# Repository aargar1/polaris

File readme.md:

# Polaris
Polaris is a feature-rich development board built around the Lattice iCE40 FPGA, designed for experimentation and small FPGA-based projects. The board provides a practical set of peripherals for graphics, storage, and USB-based interaction, all in a compact and approachable design. I designed it to implement a custom 32-bit microcontroller.

## Features

- Lattice iCE40 FPGA
- VGA output with audio support
- SD card interface
- 2× USB Type-A ports
- User-controllable LED
- GPIO and SPI headers

## Tooling

Polaris is plug-and-play compatable with the `yosys` toolchain. The [iCEStudio](https://icestudio.io/) development enviornment provides a great ecosystem for development on Polaris and iCE40-based boards in general.

## Acknowlegments

Thanks to the open-source FPGA and KiCad communities, whose tools and documentation made this project possible.

## BOM (Hack Club Blueprint)
| Comment             | Designator                      | Footprint        | LCSC Part # | Direct Link                                                                                              |
| ------------------- | ------------------------------- | ---------------- | ----------- | -------------------------------------------------------------------------------------------------------- |
| 2150                | R11,R3,R7                       | 0603             | C2960889    | [https://www.lcsc.com/product-detail/C2960889.html](https://www.lcsc.com/product-detail/C2960889.html)   |
| 2.7nF               | C15,C16                         | 0603             | C1609       | [https://www.lcsc.com/product-detail/C1609.html](https://www.lcsc.com/product-detail/C1609.html)         |
| Bus                 | J4                              | 2x14 2.54mm      | C725886     | [https://www.lcsc.com/product-detail/C725886.html](https://www.lcsc.com/product-detail/C725886.html)     |
| VGA                 | J1                              | ICD15S13E4GV00LF | C3121412    | [https://www.lcsc.com/product-detail/C3121412.html](https://www.lcsc.com/product-detail/C3121412.html)   |
| 74CBTLV3126PW,118   | U2                              | TSSOP-14         | C478017     | [https://www.lcsc.com/product-detail/C478017.html](https://www.lcsc.com/product-detail/C478017.html)     |
| 47k                 | R17,R19–R24,R27,R30,R31         | 0603             | C25819      | [https://www.lcsc.com/product-detail/C25819.html](https://www.lcsc.com/product-detail/C25819.html)       |
| WM8524CGEDT         | U3                              | TSSOP-16         | C146242     | [https://www.lcsc.com/product-detail/C146242.html](https://www.lcsc.com/product-detail/C146242.html)     |
| 1Ω                  | R28,R29                         | 0603             | C22936      | [https://www.lcsc.com/product-detail/C22936.html](https://www.lcsc.com/product-detail/C22936.html)       |
| NRS4018T2R2MDGJ     | L1                              | SRN4018          | C92959      | [https://www.lcsc.com/product-detail/C92959.html](https://www.lcsc.com/product-detail/C92959.html)       |
| W25Q16JVSNIQ        | U4                              | SOIC-8           | C115407     | [https://www.lcsc.com/product-detail/C115407.html](https://www.lcsc.com/product-detail/C115407.html)     |
| 330Ω                | R35,R36,R37                     | 0603             | C23138      | [https://www.lcsc.com/product-detail/C23138.html](https://www.lcsc.com/product-detail/C23138.html)       |
| TLV62568DBVR        | U7                              | SOT-23-5         | C163219     | [https://www.lcsc.com/product-detail/C163219.html](https://www.lcsc.com/product-detail/C163219.html)     |
| 100nF               | C1,C2,C3,C4,C5,C10,C14,C27,C30  | 0603             | C14663      | [https://www.lcsc.com/product-detail/C14663.html](https://www.lcsc.com/product-detail/C14663.html)       |
| SW_Push             | SW1                             | 6mm              | C455112     | [https://www.lcsc.com/product-detail/C455112.html](https://www.lcsc.com/product-detail/C455112.html)     |
| 1.5k                | R32,R33                         | 0603             | C22843      | [https://www.lcsc.com/product-detail/C22843.html](https://www.lcsc.com/product-detail/C22843.html)       |
| USB_A               | J5,J6                           | XKB U231-091N    | C2880618    | [https://www.lcsc.com/product-detail/C2880618.html](https://www.lcsc.com/product-detail/C2880618.html)   |
| 4.7uF               | C6,C7,C8,C9,C17,C18,C19         | 0603             | C19666      | [https://www.lcsc.com/product-detail/C19666.html](https://www.lcsc.com/product-detail/C19666.html)       |
| ICE40UP5K-SG48I     | U1                              | QFN-48           | C2678152    | [https://www.lcsc.com/product-detail/C2678152.html](https://www.lcsc.com/product-detail/C2678152.html)   |
| Flashenable         | JP1                             | 1x02 2.54mm      | C5360898    | [https://www.lcsc.com/product-detail/C5360898.html](https://www.lcsc.com/product-detail/C5360898.html)   |
| LED_BGKR            | D1                              | 5mm RGB          | C7117555    | [https://www.lcsc.com/product-detail/C7117555.html](https://www.lcsc.com/product-detail/C7117555.html)   |
| 820Ω                | R13,R14                         | 0603             | C23253      | [https://www.lcsc.com/product-detail/C23253.html](https://www.lcsc.com/product-detail/C23253.html)       |
| 10uF                | C23,C24,C25,C26,C28,C29,C31,C32 | 0805             | C15850      | [https://www.lcsc.com/product-detail/C15850.html](https://www.lcsc.com/product-detail/C15850.html)       |
| 560Ω                | R25,R26                         | 0603             | C23204      | [https://www.lcsc.com/product-detail/C23204.html](https://www.lcsc.com/product-detail/C23204.html)       |
| 536Ω                | R1,R5,R9                        | 0603             | C23201      | [https://www.lcsc.com/product-detail/C23201.html](https://www.lcsc.com/product-detail/C23201.html)       |
| SX5M25.000M20F30TNN | X1                              | 25MHz Osc        | C2901535    | [https://www.lcsc.com/product-detail/C2901535.html](https://www.lcsc.com/product-detail/C2901535.html)   |
| MIC5504-3.3YM5      | U8                              | SOT-23-5         | C41348078   | [https://www.lcsc.com/product-detail/C41348078.html](https://www.lcsc.com/product-detail/C41348078.html) |
| Prog                | J2                              | 1x08 2.54mm      | C5156616    | [https://www.lcsc.com/product-detail/C5156616.html](https://www.lcsc.com/product-detail/C5156616.html)   |
| FerriteBead_Small   | FB1,FB2                         | 0603             | C1027       | [https://www.lcsc.com/product-detail/C1027.html](https://www.lcsc.com/product-detail/C1027.html)         |
| 4300Ω               | R12,R4,R8                       | 0603             | C23159      | [https://www.lcsc.com/product-detail/C23159.html](https://www.lcsc.com/product-detail/C23159.html)       |
| 1uF                 | C12,C13                         | 0603             | C15849      | [https://www.lcsc.com/product-detail/C15849.html](https://www.lcsc.com/product-detail/C15849.html)       |
| 2.2uF               | C11                             | 0603             | C23630      | [https://www.lcsc.com/product-detail/C23630.html](https://www.lcsc.com/product-detail/C23630.html)       |
| 10k                 | R15,R16,R18,R34                 | 0603             | C25804      | [https://www.lcsc.com/product-detail/C25804.html](https://www.lcsc.com/product-detail/C25804.html)       |
| 1070Ω               | R10,R2,R6                       | 0603             | C177957     | [https://www.lcsc.com/product-detail/C177957.html](https://www.lcsc.com/product-detail/C177957.html)     |
| Barrel_Jack         | J7                              | PJ-063AH         | C22434582   | [https://www.lcsc.com/product-detail/C22434582.html](https://www.lcsc.com/product-detail/C22434582.html) |
| SD_Card             | J3                              | 693063010911     | C341097     | [https://www.lcsc.com/product-detail/C341097.html](https://www.lcsc.com/product-detail/C341097.html)     |
| SN74AHC00PWR        | U9                              | TSSOP-14         | C8143       | [https://www.lcsc.com/product-detail/C8143.html](https://www.lcsc.com/product-detail/C8143.html)         |

## License
This project is licensed under the CERN Open Hardware Licence Version 2. If you would like to use Assemblage for a patently non-commercial or educational application, but cannot do so under this license, please contact me via an issue; I would be happy to work something out.

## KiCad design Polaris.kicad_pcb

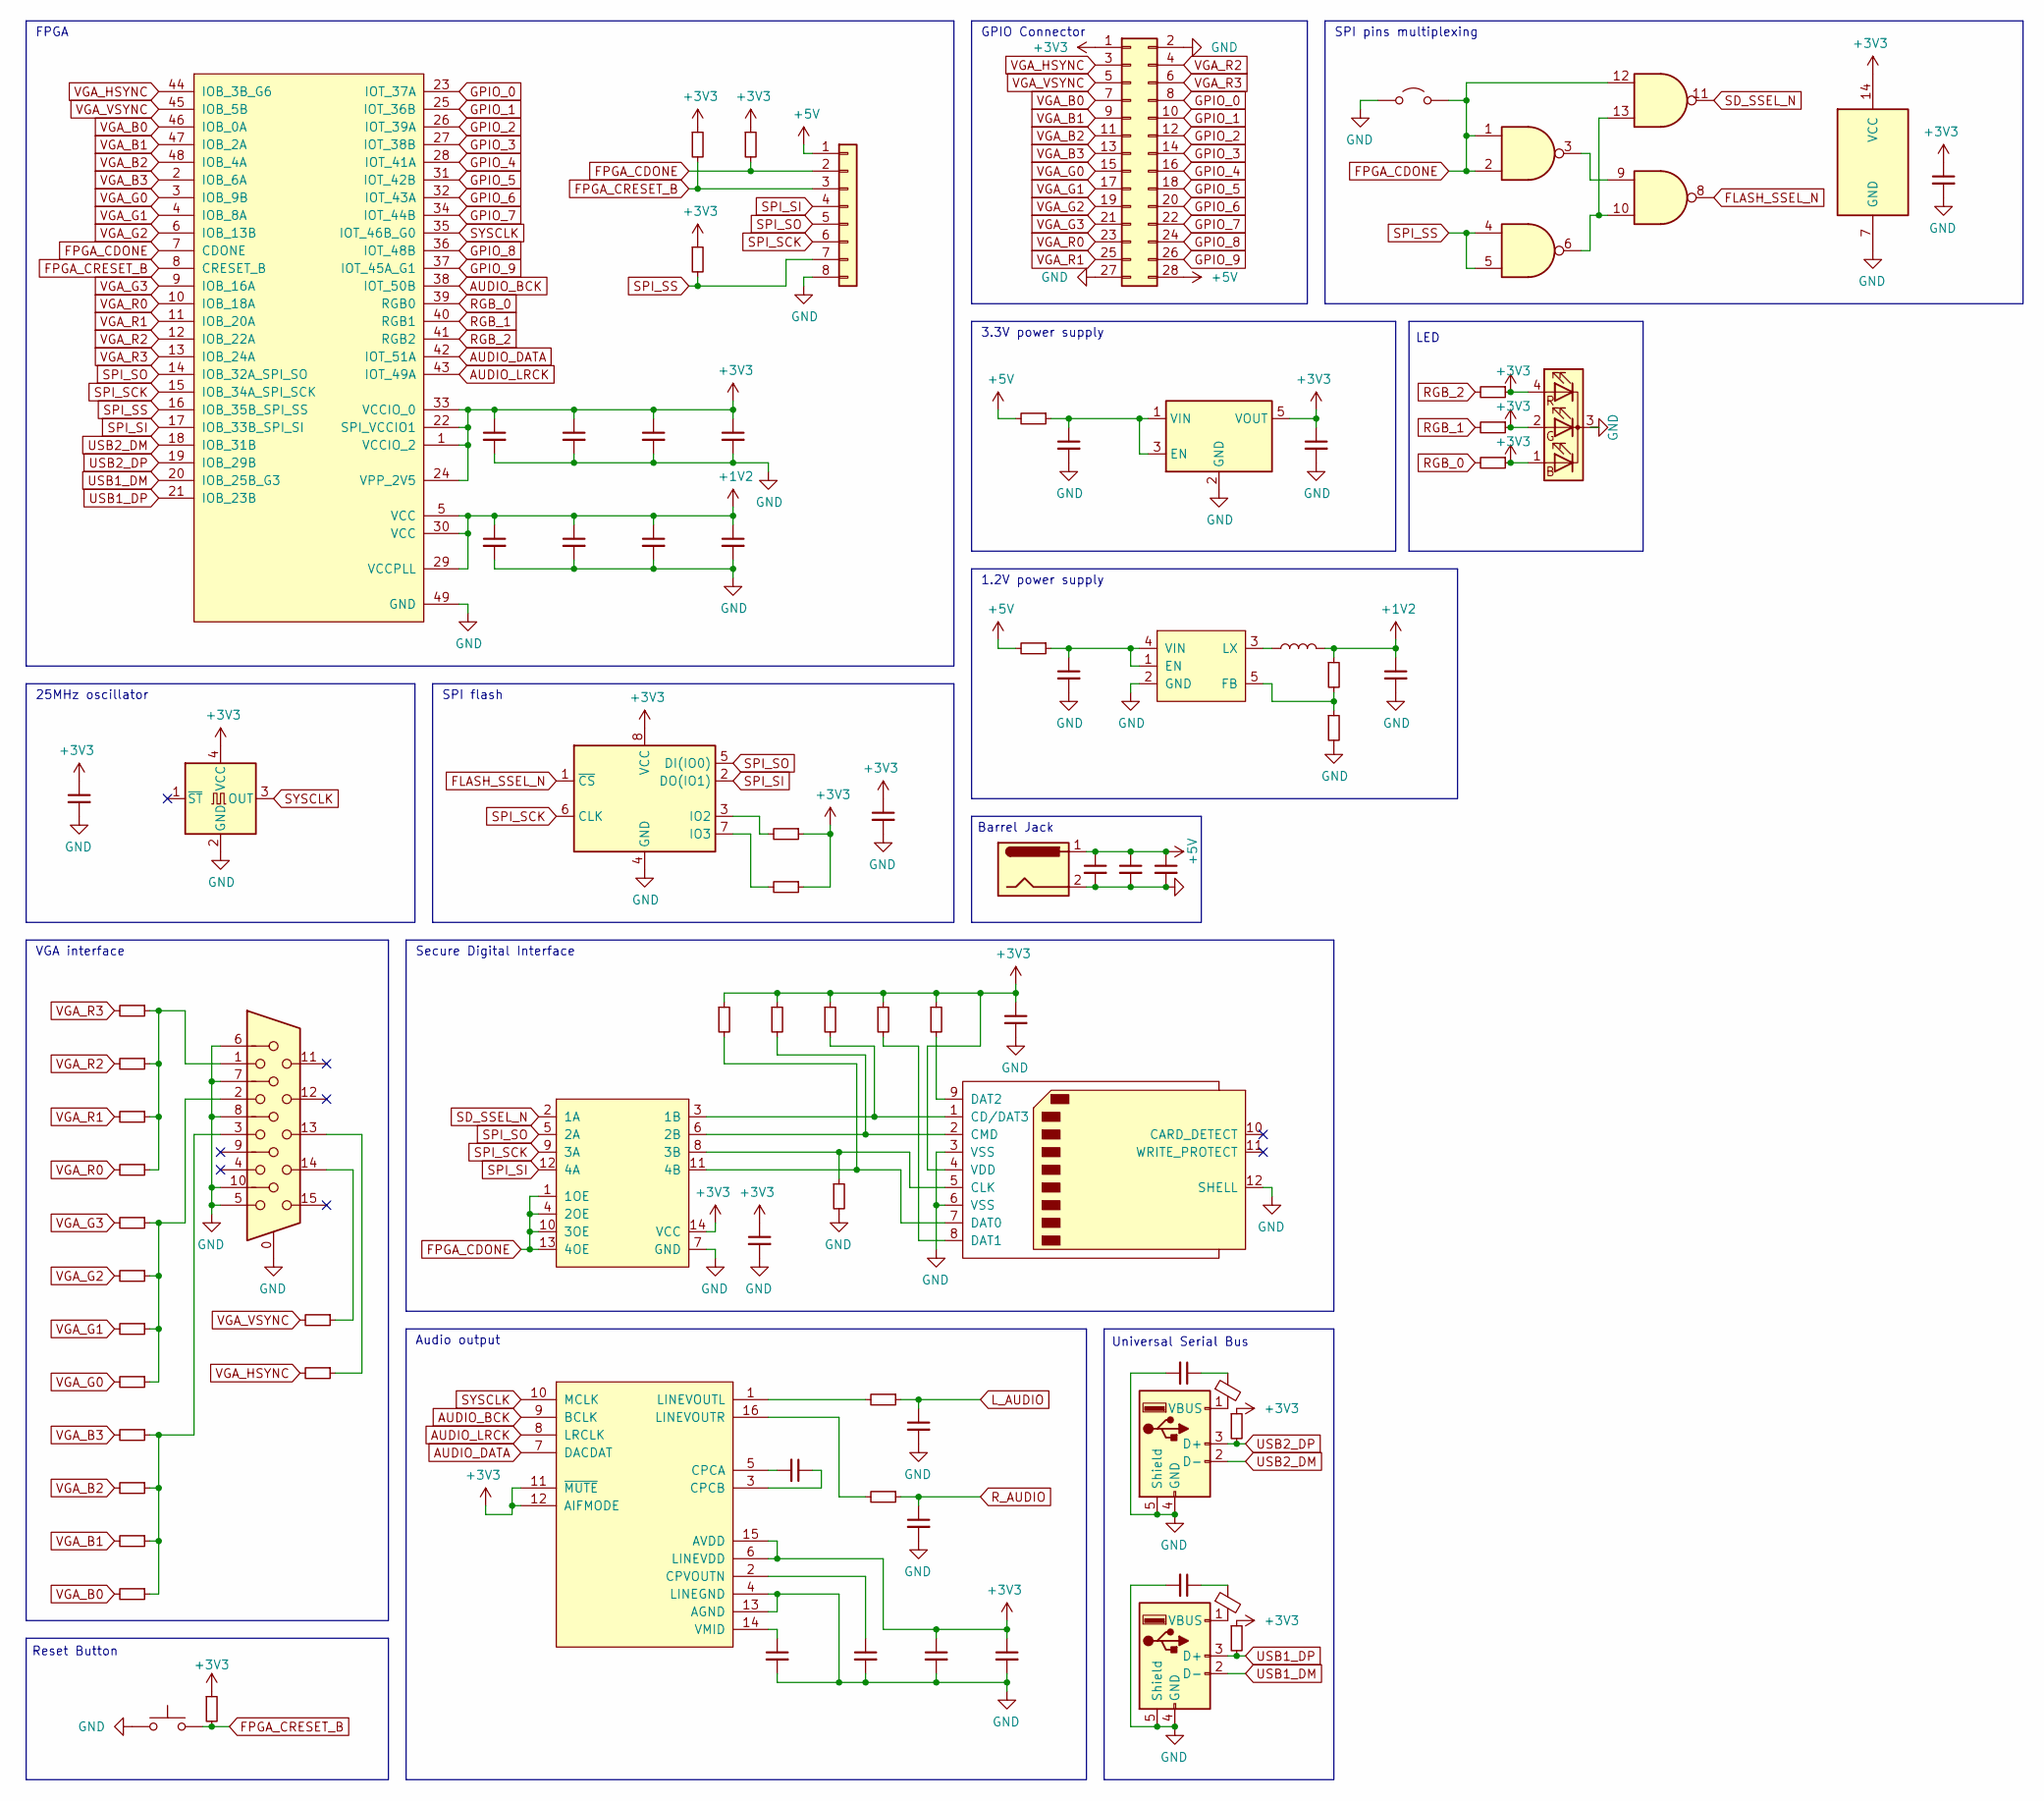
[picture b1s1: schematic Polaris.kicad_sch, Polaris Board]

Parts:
C1, C2, C3, C4, C5, C10, C14, C27, C30: 100nF; C_0603_1608Metric
C6, C7, C8, C9, C17, C18, C19: 4.7uF; C_0603_1608Metric
C11: 2.2uF; C_0603_1608Metric
C12: 1u; C_0603_1608Metric
C13: 1uF; C_0603_1608Metric
C15, C16: 2.7nF; C_0603_1608Metric
C23, C24, C25, C26, C28, C29, C31, C32: 10uF; C_0805_2012Metric
D1: LED_BGKR; LED_D5.0mm-4_RGB_Wide_Pins
FB1, FB2: FerriteBead_Small; L_0603_1608Metric
J1: VGA; ICD15S13E4GV00LF
J2: Prog; PinHeader_1x08_P2.54mm_Vertical
J3: SD_Card; 693063010911
J4: Bus; PinHeader_2x14_P2.54mm_Vertical
J5, J6: USB_A; USB_A_Receptacle_XKB_U231-091N-4BLRA00-S
J7: Barrel_Jack; BarrelJack_CUI_PJ-063AH_Horizontal
JP1: Flash enable; PinHeader_1x02_P2.54mm_Vertical
L1: NRS4018T2R2MDGJ; L_Bourns-SRN4018
R1, R5, R9: 536; R_0603_1608Metric
R2, R6, R10: 1070; R_0603_1608Metric
R3, R7, R11: 2150; R_0603_1608Metric
R4, R8, R12: 4300; R_0603_1608Metric
R13, R14: 820; R_0603_1608Metric
R15, R16, R18, R34: 10k; R_0603_1608Metric
R17, R19, R20, R21, R22, R23, R24, R27, R30, R31: 47k; R_0603_1608Metric
R25, R26: 560; R_0603_1608Metric
R28, R29: 1; R_0603_1608Metric
R32, R33: 1.5k; R_0603_1608Metric
R35, R36, R37: 330; R_0603_1608Metric
SW1: SW_Push; SW_PUSH_6mm
U1: ICE40UP5K-SG48I; QFN-48-1EP_7x7mm_P0.5mm_EP5.3x5.3mm
U2: 74CBTLV3126PW,118; TSSOP-14_4.4x5mm_P0.65mm
U3: WM8524CGEDT; TSSOP-16_4.4x5mm_P0.65mm
U4: W25Q16JVSNIQ; SOIC-8_3.9x4.9mm_P1.27mm
U7: TLV62568DBVR; SOT-23-5
U8: MIC5504-3.3YM5; SOT-23-5
U9: SN74AHC00PWR; TSSOP-14_4.4x5mm_P0.65mm
X1: SX5M25.000M20F30TNN; Oscillator_SMD_SeikoEpson_SG8002LB-4Pin_5.0x3.2mm

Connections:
+1V2: C3.1, C5.1, C7.1, C9.1, C26.1, L1.2, R30.1, U1.5 (VCC), U1.29 (VCCPLL), U1.30 (VCC)
+3V3: C1.1, C2.1, C4.1, C6.1, C8.1, C10.1, C14.1, C17.1, C18.1, C19.1, C25.1, C27.1, D1.1 (BA), D1.2 (GA), D1.4 (RA), J3.4 (VDD), J4.1, R15.1, R16.1, R17.1, R18.1, R19.1, R20.1, R21.1, R22.1, R24.1, R27.1, R32.1, R33.1, R34.1, R35.1, R36.1, R37.1, U1.1 (VCCIO_2), U1.22 (SPI_VCCIO1), U1.24 (VPP_2V5), U1.33 (VCCIO_0), U2.14 (VCC), U3.6 (LINEVDD), U3.11 (~MUTE), U3.12 (AIFMODE), U3.15 (AVDD), U4.8 (VCC), U8.5 (VOUT), U9.14 (VCC), X1.4 (VCC)
+5V: C30.1, C31.1, C32.1, J2.1, J4.28, J7.1, R28.2, R29.2
AUDIO_BCK: U1.38 (IOT_50B), U3.9 (BCLK)
AUDIO_DATA: U1.42 (IOT_51A), U3.7 (DACDAT)
AUDIO_LRCK: U1.43 (IOT_49A), U3.8 (LRCLK)
FLASH_SSEL_N: U4.1 (~CS), U9.8
FPGA_CDONE: J2.2, JP1.2 (B), R18.2, U1.7 (CDONE), U2.1 (1OE), U2.4 (2OE), U2.10 (3OE), U2.13 (4OE), U9.1, U9.2, U9.12
FPGA_CRESET_B: J2.3, R15.2, R34.2, SW1.2, U1.8 (CRESET_B)
GND: C1.2, C2.2, C3.2, C4.2, C5.2, C6.2, C7.2, C8.2, C9.2, C10.2, C11.2, C13.2, C14.2, C15.2, C16.2, C17.2, C18.2, C19.2, C23.2, C24.2, C25.2, C26.2, C27.2, C28.2, C29.2, C30.2, C31.2, C32.2, D1.3 (K), J1.0, J1.5, J1.6, J1.7, J1.8, J1.10, J2.8, J3.3 (VSS), J3.6 (VSS), J3.12 (SHELL), J4.2, J4.27, J5.4 (GND), J5.5 (Shield), J6.4 (GND), J6.5 (Shield), J7.2, JP1.1 (A), R23.2, R31.2, SW1.1, U1.49 (GND), U2.7 (GND), U3.4 (LINEGND), U3.13 (AGND), U4.4 (GND), U7.2 (GND), U8.2 (GND), U9.7 (GND), X1.2 (GND)
GPIO_0: J4.8, U1.23 (IOT_37A)
GPIO_1: J4.10, U1.25 (IOT_36B)
GPIO_2: J4.12, U1.26 (IOT_39A)
GPIO_3: J4.14, U1.27 (IOT_38B)
GPIO_4: J4.16, U1.28 (IOT_41A)
GPIO_5: J4.18, U1.31 (IOT_42B)
GPIO_6: J4.20, U1.32 (IOT_43A)
GPIO_7: J4.22, U1.34 (IOT_44B)
GPIO_8: J4.24, U1.36 (IOT_48B)
GPIO_9: J4.26, U1.37 (IOT_45A_G1)
L_AUDIO: C15.1, R25.1
unnamed: C28.1, FB1.1
unnamed: C29.1, FB2.1
unnamed: J1.1, R1.1, R2.1, R3.1, R4.1
unnamed: J1.2, R5.1, R6.1, R7.1, R8.1
unnamed: J1.3, R9.1, R10.1, R11.1, R12.1
unnamed: J1.13, R14.1
unnamed: J1.14, R13.1
unnamed: J3.1 (CD/DAT3), R22.2, U2.3 (1B)
unnamed: J3.5 (CLK), R23.1, U2.8 (3B)
unnamed: J3.2 (CMD), R19.2, U2.6 (2B)
unnamed: J3.7 (DAT0), R17.2, U2.11 (4B)
unnamed: J3.8 (DAT1), R24.2
unnamed: J3.9 (DAT2), R27.2
unnamed: FB1.2, J5.1 (VBUS)
unnamed: FB2.2, J6.1 (VBUS)
unnamed: C12.2, U3.5 (CPCA)
unnamed: C12.1, U3.3 (CPCB)
unnamed: C13.1, U3.2 (CPVOUTN)
unnamed: R25.2, U3.1 (LINEVOUTL)
unnamed: R26.2, U3.16 (LINEVOUTR)
unnamed: C11.1, U3.14 (VMID)
unnamed: R20.2, U4.3 (IO2)
unnamed: R21.2, U4.7 (IO3)
unnamed: C24.1, R29.1, U7.1 (EN), U7.4 (VIN)
unnamed: R30.2, R31.1, U7.5 (FB)
unnamed: L1.1, U7.3 (LX)
unnamed: C23.1, R28.1, U8.1 (VIN), U8.3 (EN)
unnamed: U9.3, U9.9
unnamed: U9.6, U9.10, U9.13
RGB_0: R37.2, U1.39 (RGB0)
RGB_1: R36.2, U1.40 (RGB1)
RGB_2: R35.2, U1.41 (RGB2)
R_AUDIO: C16.1, R26.1
SD_SSEL_N: U2.2 (1A), U9.11
SPI_SCK: J2.6, U1.15 (IOB_34A_SPI_SCK), U2.9 (3A), U4.6 (CLK)
SPI_SI: J2.4, U1.17 (IOB_33B_SPI_SI), U2.12 (4A), U4.2 (DO(IO1))
SPI_SO: J2.5, U1.14 (IOB_32A_SPI_SO), U2.5 (2A), U4.5 (DI(IO0))
SPI_SS: J2.7, R16.2, U1.16 (IOB_35B_SPI_SS), U9.4, U9.5
SYSCLK: U1.35 (IOT_46B_G0), U3.10 (MCLK), X1.3 (OUT)
USB1_DM: J6.2 (D-), U1.20 (IOB_25B_G3)
USB1_DP: J6.3 (D+), R33.2, U1.21 (IOB_23B)
USB2_DM: J5.2 (D-), U1.18 (IOB_31B)
USB2_DP: J5.3 (D+), R32.2, U1.19 (IOB_29B)
VGA_B0: J4.7, R12.2, U1.46 (IOB_0A)
VGA_B1: J4.9, R11.2, U1.47 (IOB_2A)
VGA_B2: J4.11, R10.2, U1.48 (IOB_4A)
VGA_B3: J4.13, R9.2, U1.2 (IOB_6A)
VGA_G0: J4.15, R8.2, U1.3 (IOB_9B)
VGA_G1: J4.17, R7.2, U1.4 (IOB_8A)
VGA_G2: J4.19, R6.2, U1.6 (IOB_13B)
VGA_G3: J4.21, R5.2, U1.9 (IOB_16A)
VGA_HSYNC: J4.3, R14.2, U1.44 (IOB_3B_G6)
VGA_R0: J4.23, R4.2, U1.10 (IOB_18A)
VGA_R1: J4.25, R3.2, U1.11 (IOB_20A)
VGA_R2: J4.4, R2.2, U1.12 (IOB_22A)
VGA_R3: J4.6, R1.2, U1.13 (IOB_24A)
VGA_VSYNC: J4.5, R13.2, U1.45 (IOB_5B)

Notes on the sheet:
25MHz oscillator
VGA interface
SPI pins multiplexing
Secure Digital Interface
Audio output
Reset Button
Universal Serial Bus
1.2V power supply
LED
FPGA
SPI flash
3.3V power supply
GPIO Connector
Barrel Jack

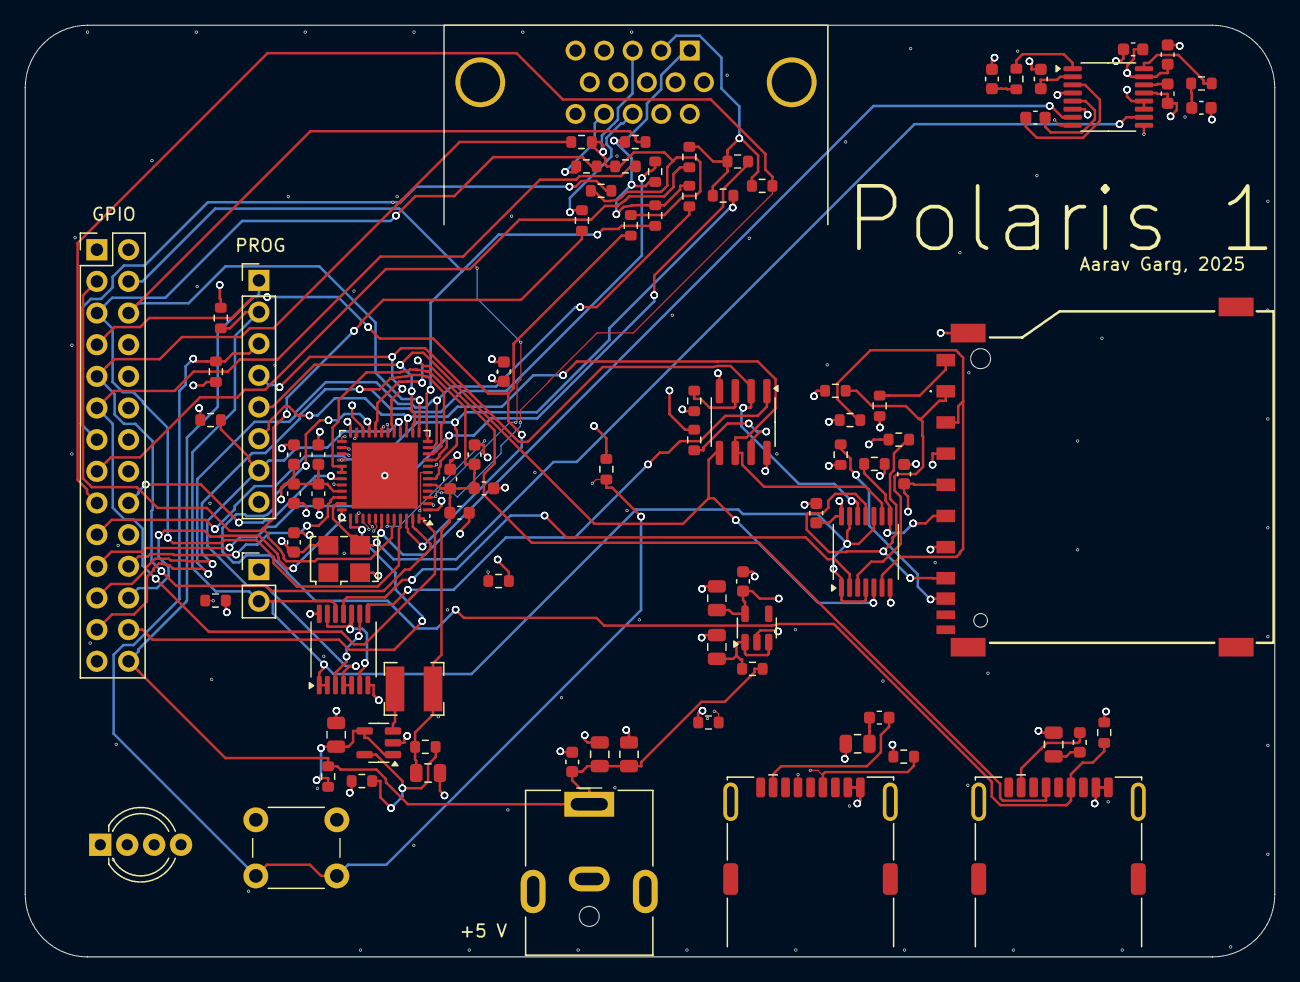
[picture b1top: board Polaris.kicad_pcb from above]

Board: 6 copper layers, 100.2 x 74.8 mm, 87 parts (0 on the bottom side), 78 nets.

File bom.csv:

Comment,Designator,Footprint,LCSC Part #
2150,"R11,R3,R7",0603,C2960889
2.7nF,"C15,C16",0603,C1609
Bus,J4,PinHeader_2x14_P2.54mm_Vertical,C725886
VGA,J1,ICD15S13E4GV00LF,C3121412
74CBTLV3126PW,118,U2,TSSOP-14_4.4x5mm_P0.65mm,C478017
47k,"R17,R19,R20,R21,R22,R23,R24,R27,R30,R31",0603,C25819
WM8524CGEDT,U3,TSSOP-16_4.4x5mm_P0.65mm,C146242
1,"R28,R29",0603,C22936
NRS4018T2R2MDGJ,L1,L_Bourns-SRN4018,C92959
W25Q16JVSNIQ,U4,SOIC-8_3.9x4.9mm_P1.27mm,C115407
330,"R35,R36,R37",0603,C23138
TLV62568DBVR,U7,SOT-23-5,C163219
100nF,"C1,C10,C14,C2,C27,C3,C30,C4,C5",0603,C14663
SW_Push,SW1,SW_PUSH_6mm,C455112
1.5k,"R32,R33",0603,C22843
USB_A,"J5,J6",USB_A_Receptacle_XKB_U231-091N-4BLRA00-S,C2880618
4.7uF,"C17,C18,C19,C6,C7,C8,C9",0603,C19666
ICE40UP5K-SG48I,U1,QFN-48-1EP_7x7mm_P0.5mm_EP5.3x5.3mm,C2678152
Flashenable,JP1,PinHeader_1x02_P2.54mm_Vertical,C5360898
LED_BGKR,D1,LED_D5.0mm-4_RGB_Wide_Pins,C7117555
820,"R13,R14",0603,C23253
10uF,"C23,C24,C25,C26,C28,C29,C31,C32",0805,C15850
560,"R25,R26",0603,C23204
536,"R1,R5,R9",0603,C23201
SX5M25.000M20F30TNN,X1,Oscillator_SMD_SeikoEpson_SG8002LB-4Pin_5.0x3.2mm,C2901535
MIC5504-3.3YM5,U8,SOT-23-5,C41348078
Prog,J2,PinHeader_1x08_P2.54mm_Vertical,C5156616
FerriteBead_Small,"FB1,FB2",0603,C1027
4300,"R12,R4,R8",0603,C23159
1u,"C12,C13",0603,C15849
2.2uF,C11,0603,C23630
10k,"R15,R16,R18,R34",0603,C25804
1070,"R10,R2,R6",0603,C177957
Barrel_Jack,J7,BarrelJack_CUI_PJ-063AH_Horizontal,C22434582
SD_Card,J3,693063010911,C341097
SN74AHC00PWR,U9,TSSOP-14_4.4x5mm_P0.65mm,C8143

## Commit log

2026-01-04 Add CERN Open Hardware Licence to README
    Added CERN Open Hardware Licence Version 2 - Weakly Reciprocal to README.
2026-01-04 Rename README.md to license
2026-01-04 Add initial README for Polaris development board
2026-02-26 Add BOM with components and specifications
    Added bill of materials with component details.

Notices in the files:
Polaris.kicad_sch:
All Rights Reserved; See license for details.
